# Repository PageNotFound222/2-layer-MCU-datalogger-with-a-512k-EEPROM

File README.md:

# 2-layer-MCU-datalogger-with-a-512k-EEPROM
# 📟 MCU Data Logger with 512KB EEPROM

## 📌 Overview

This project is a **microcontroller-based data logging system** designed to capture, store, and retrieve data using an external **512KB EEPROM**. The system ensures **non-volatile storage**, making it suitable for applications where data must persist even after power loss.

The logger collects data from input sources (sensors or internal signals), processes it, and stores it efficiently in EEPROM using structured memory management techniques.

---

## ⚙️ System Architecture

The system consists of the following core components:

* **Microcontroller (MCU)**
  Handles data acquisition, processing, and communication with EEPROM.

* **External EEPROM (512KB)**
  Stores logged data in a non-volatile format.

* **Communication Interface**
  Used for data transfer (e.g., UART / I2C / SPI).

---

## 🔄 Working Principle

### 1. Data Acquisition

The MCU reads input signals such as:

* Analog sensor data (via ADC)
* Digital inputs
* Internal system parameters

---

### 2. Data Formatting

Before storing, the data is structured into fixed-size records:

```
[Timestamp][Sensor Data][Status][Checksum]
```

This ensures consistency and simplifies retrieval.

---

### 3. EEPROM Storage

The EEPROM acts as a **byte-addressable memory space**:

* Total Size: **512 KB (524,288 bytes)**
* Data is written sequentially using a **write pointer**

---

### 4. Memory Management

#### 📍 Memory Map Example

```
0x0000 – 0x0FFF   → Configuration Data
0x1000 – End      → Logged Data
```

---
---

### 6. Data Retrieval

Stored data can be read:

* Sequentially from EEPROM
* Transmitted via communication interface (e.g., UART)

---

## 🧠 Key Design Concepts

### ✅ Non-Volatile Storage

EEPROM retains data even after power loss.

---

### ⚠️ Write Cycle Limitation

EEPROM has limited write endurance (~1 million cycles per address).

#### Solution:

* Implement **wear leveling**
* Avoid repeated writes to the same location

---

### ⚡ Write Latency

EEPROM write operations are relatively slow.

#### Solution:

* Use **RAM buffering**
* Batch writes instead of frequent single writes

---

### 🔐 Data Integrity

Power loss during write may corrupt data.
---

## 📊 Storage Capacity

Example:

* Record Size: 16 bytes
* Total Memory: 524,288 bytes

```
Total Records ≈ 524,288 / 16 = 32,768 entries
```

---
## 🧪 Features

* Efficient EEPROM memory utilization
* Circular buffer logging system
* Data integrity via checksum
* Modular firmware design
* Scalable architecture for multiple sensors

---

## 🚧 Challenges & Solutions

| Challenge        | Solution            |
| ---------------- | ------------------- |
| EEPROM wear      | Wear leveling       |
| Slow write speed | RAM buffering       |
| Power failure    | Checksum validation |
| Memory overflow  | Circular buffer     |

---

## 🚀 Applications

* IoT Data Logging
* Environmental Monitoring
* Industrial Systems
* Black Box Recording Systems

---

## 📎 Future Improvements

* Add SD card support for larger storage
* Implement real-time clock (RTC)
* Wireless data transmission (BLE/WiFi)
* Advanced compression techniques

---

## 📜 License

This project is open-source and available under the MIT License.

---

## 👨‍💻 Author

Developed by a second year electronics student so forgive me if there is any issue

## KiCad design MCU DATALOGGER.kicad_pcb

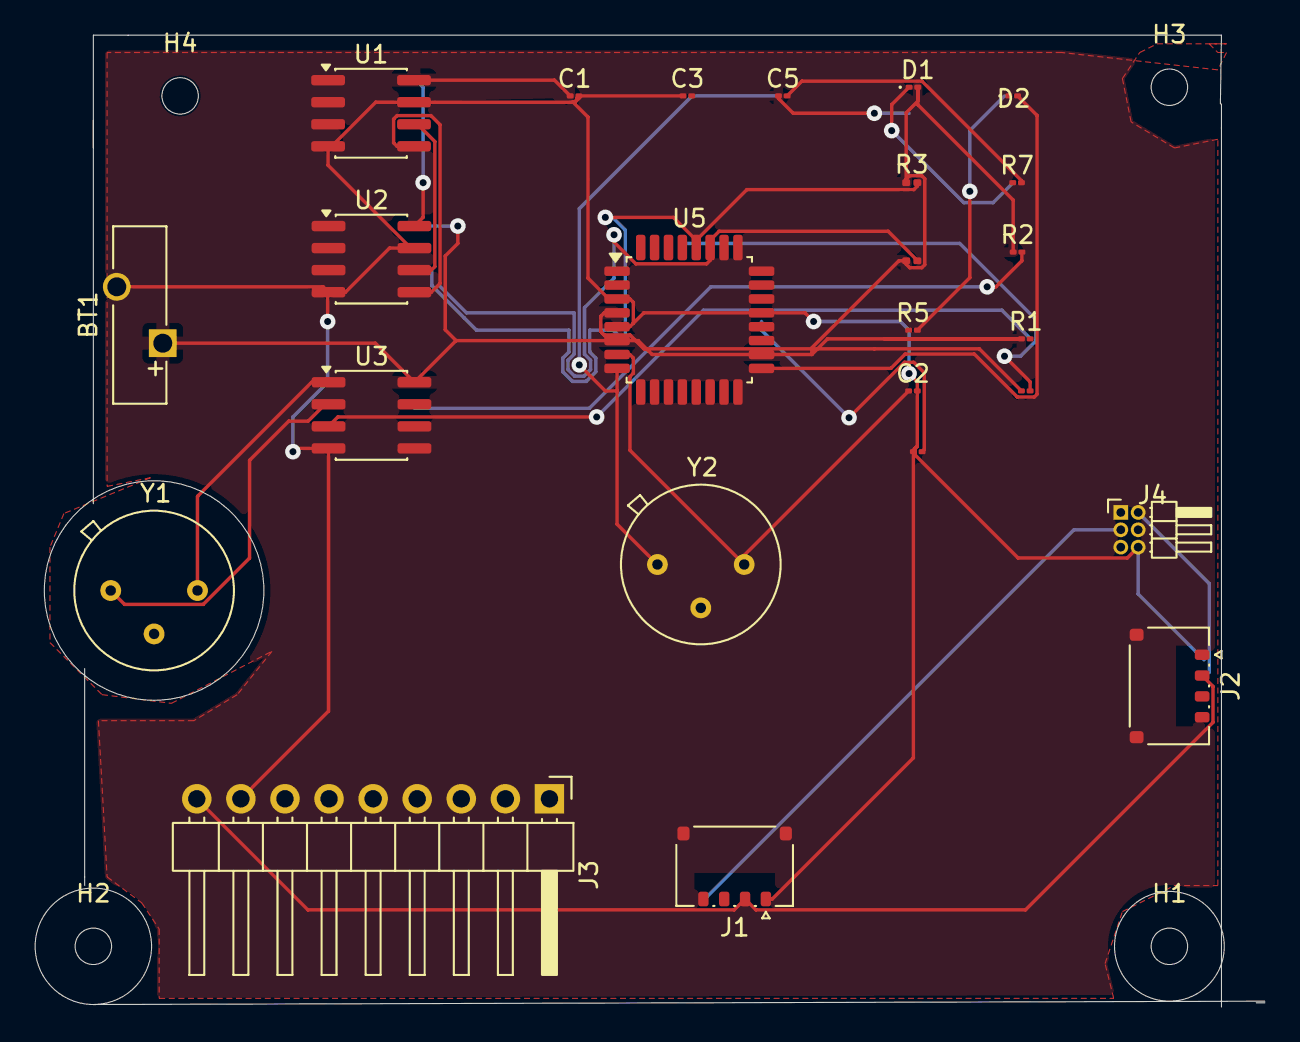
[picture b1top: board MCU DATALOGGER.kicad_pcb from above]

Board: 2 copper layers, 70.9 x 56.0 mm, 29 parts (0 on the bottom side), 17 nets.

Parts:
BT1: Battery; Battery_Panasonic_CR1025-VSK_Vertical_CircularHoles
C1, C4: 0.1uF; C_01005_0402Metric
C2, C3: 22pF; C_01005_0402Metric
C5: 100nF; C_01005_0402Metric
D1, D2: LED; LED_01005_0402Metric
H1, H2, H3, H4: MountingHole; MountingHole_2.1mm
J1, J2: Conn_01x04_Pin; Hirose_DF57H-4P-1.2V_1x04_P1.2mm_Socket
J3: Conn_01x09_Pin; PinHeader_1x09_P2.54mm_Horizontal
J4: Conn_02x03_Odd_Even; PinHeader_2x03_P1.00mm_Horizontal
R1, R2, R6: 10K; R_01005_0402Metric
R3, R4: 4.7K; R_0201_0603Metric
R5, R7: 330; R_01005_0402Metric
U1, U2: 24LC1025; SOIC-8_3.9x4.9mm_P1.27mm
U3: DS1337S_; SOIC-8_3.9x4.9mm_P1.27mm
U5: ATMEGA328P-AU; TQFP-32_7x7mm_P0.8mm
Y1: 32.768 Khz; Crystal_HC35-U
Y2: 16Mhz; Crystal_HC35-U

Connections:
/RESET: R6.2, U5.29 (PC6/~RESET)
/SCK: R3.2, U1.6 (SCL), U2.6 (SCL), U5.28 (PC5)
/SDA: R4.2, U1.5 (SDA), U2.5 (SDA), U5.27 (PC4)
/connectors/SCK: J1.4, J4.3
/connectors/Vcc: J1.2, J2.2, J3.9, J4.2
GND: BT1.2 (-), C1.2, C2.2, C3.1, C4.1, C5.2, J1.1, J2.1, J3.8, J4.6, R5.1, R7.2, U1.4 (GND), U1.7 (WP), U2.4 (GND), U2.7 (WP), U3.4 (GND), U5.3 (GND), U5.5 (GND), U5.21 (GND)
unnamed: D1.2 (A), U5.17 (PB5)
unnamed: D1.1 (K), R5.2
unnamed: D2.1 (K), R7.1
unnamed: R2.2, U3.7 (SQW/~INT)
unnamed: U3.1 (X1), Y1.2
unnamed: U3.2 (X2), Y1.1
unnamed: R1.2, U3.3 (~INTA)
unnamed: C4.2, U5.20 (AREF)
unnamed: C2.1, U5.7 (PB6), Y2.2
unnamed: C3.2, U5.8 (PB7), Y2.1
VCC: BT1.1 (+), C1.1, C5.1, D2.2 (A), R1.1, R2.1, R3.1, R4.1, R6.1, U1.8 (VCC), U2.8 (VCC), U3.8 (VCC), U5.4 (VCC), U5.6 (VCC), U5.18 (AVCC)
